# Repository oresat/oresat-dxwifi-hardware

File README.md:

# oresat-dxwifi-hardware
This repository is for the DxWiFi hardware that will fly on the OreSat satellite. DxWiFi is our communication subsystem for high speed data (1 Mbps) using 2.4 GHz WiFi between the spacecraft and ground.

This is hardware for the **satellite** only; please see the other repos if you're looking for the [OreSat Live Handheld Ground Station](https://github.com/oresat/oresat-live-handheld-ground-station) or the [Mini-OreSat testing platform for high altitude balloons](https://github.com/oresat/oresat-live-mini-oresat).

We intend to use "ordinary WiFi" (IEEE 802.11b) as a high speed satellite communication system. What is _not_ ordinary is that we run the radio under the amateur radio rules and regulations (FCC Part 97) and thus can increase power levels and antenna gains necessary to make the link budget work.

### Ordinary WiFi
The plan is to use the Qualcomm Atheros AR9271 USB to WiFi adapter because of the driver support in Linux.

### Non ordinary bi-directional power amplifier
This project is intended to operate under the Amateur Radio Service [47CFR97](https://www.gpo.gov/fdsys/pkg/CFR-1996-title47-vol5/pdf/CFR-1996-title47-vol5-part97.pdf) whereby larger power levels and higher gain directional antennas can be used within the [13 cm band](https://en.wikipedia.org/wiki/13-centimeter_band) to close the link.

NB:  There are other DxWiFi materials on the PSAS GitHub repo, but those repos are deprecated.

Link budgets can be found [here](https://github.com/oresat/oresat-dxwifi-hardware/tree/master/Link-Model).

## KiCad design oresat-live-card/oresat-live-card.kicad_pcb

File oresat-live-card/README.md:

---
title: "**OreSat Live / DxWiFi Card**"
subtitle: |
  **Fabrication and Assembly Information**\
  For build TIME-STAMP
fontsize: 10pt
geometry:
  - margin=0.5in
toc: true
toc-depth: 2
colorlinks: true
urlcolor: blue
---

\newpage

# About this Board

## Board Description

TODO: DESCRIBE CARD

## Documentation Links

- OL hardware Git repository: <https://github.com/oresat/oresat-dxwifi-hardware>
- OL software Git reposity: <https://github.com/oresat/oresat-dxwifi-software>
- **TODO:** OL Design Notes + Design Review Notes

## Documentation Files

| Filename                        | Notes                                    |
| ------------------------------- | ---------------------------------------- |
| README.pdf                      | This README file                         |
| PROJECT-NAME-outline.dxf        | Board outline (with holes) in DXF format |
| PROJECT-NAME-pcba.step          | 3D model of PCBA (with components)       |
| PROJECT-NAME-render-bot.jpg     | Render of the top of the 3D model        |
| PROJECT-NAME-render-bot.jpg     | Render of the bottom of the 3D model     |
| PROJECT-NAME-schematic.pdf      | PDF of board schematics                  |

## Contact Information

- Website: <https://www.oresat.org/>
- Email: <oresat@pdx.edu>
- Instagram: @pdxaerospace

## Board Renders

{width=50%}
{width=50%}

\newpage

# Printed Circuit Board (PCB) Fabrication Information

## Board Info

- 4 layer board
- Bounding box is 99.8 x 94.6 mm (3.93 x 3.72 in)
- Board thickness is 1.59 mm (0.063 inch)
- **Important:** See Materials and Stack Up sections below

## Board Requirements

- Design Rules
    - Minimum Trace / Space design rules
       - Outer layers: 0.127 mm (5.0 mil) / 0.127 mm (5.0 mil)
       - Inner layers: 0.127 mm (5.0 mil) / 0.127 mm (5.0 mil)
    - Outer dimension router tolerance: +/- 0.254 mm (10.0 mil)
    - Hole placement tolerance: +/- 0.075 mm (3.0 mil)
    - Inner tab routed slot tolerance: +/- 0.254 mm (10.0 mil)
- Drills
   - Drill Positional Tolerance: 0.051 mm (2.0 mil)
   - Drill Size tolerance: +/- 0.064 mm (2.5 mil)
- Plated/Un-plated holes
  - There are 6 un-plated (NPT) holes
  - There are 1477 plated through (PTH) holes
  - PTH minimum diameter: 0.254 mm (10 mil)
  - PTH minimum annulus: 0.102 mm (4 mil) radius
- Outline/Routing
  - Requires a 1.0 mm or smaller diameter routing bit
- Slots
  - There are no slots.
- Cutouts
  - There are no cutouts
- There are 3 fiducials on the top layer and 3 on the bottom layer.
- Panel tabs ("mouse bites")
   - Card edges must be smooth; no mouse bites or other intrusions into the card outline.
   - If external mouse bites are required, minimize and customer will remove by hand before assembly.
- If not otherwise specified, build to IPC 6012 Class 2 or better.

## Materials

- Controlled impedance
   - The stackup is critical for the performance of high speed signals on this board.
   - As long as the stackup is controlled, the board is not considered controlled impedance.
- Isola FR408HR or material with equivalent Dk.
- Board Surface treatment should be ENIG, althogh immersion Silver is acceptable.
- White silkscreen on top and bottom surface
- Taiyo PSR-4000 or equivalent soldermask on top and bottom, no requirements for color.

## Stack Up

| Layer         | Thickness           | Notes                                        |
|---------------|---------------------|----------------------------------------------|
| Top Copper    | 0.043 mm /  1.7 mil |  Layer 1 foil, 1 oz Cu after plating         |
| prepreg       | 0.200 mm /  7.9 mil |  Prepreg - Isola FR408HR 2113                |
| Layer 2       | 0.018 mm /  0.7 mil |  Layer 2 foil, 0.5 oz Cu                     |
| Core          | 0.991 mm /   39 mil |  Core Isola FR408HR                          |
| Layer 3       | 0.018 mm /  0.7 mil |  Layer 3 foil, 0.5 oz Cu                     |
| prepreg       | 0.200 mm /  7.9 mil |  Prepreg - Isola FR408HR 2113                |
| Bottom Copper | 0.043 mm /  1.7 mil |  Layer 4 foil, 1 oz copper after plating     |
| **Total Stackup** | **1.588 mm / 62.5 mil** |                                      |

## Array / Panel Information

- Coordinate with Contract Manufacturer (CM) for optimal size of this panel.
- If no feedback from CM, then produce single boards (no panel).

## Fabrication Files

### IPC-2581 File

| Filename                 | Notes                                   |
| ------------------------ | --------------------------------------- |
| PROJECT-NAME-ipc2581.xml | IPC-2581 board information file         |

### Legacy PCB Files

| Filename                      | Notes                                         |
| ------------------------------| --------------------------------------------- |
| PROJECT-NAME-Edge_Cuts.gbr    | RS274X file for the dimension (outline) layer |
| PROJECT-NAME-F_Silkscreen.gbr | RS274X file for the top silkscreen            |
| PROJECT-NAME-F_Mask.gbr       | RS274X file for the top soldermask            |
| PROJECT-NAME-F_Cu.gbr         | RS274X file for the top copper layer          |
| PROJECT-NAME-In1_Cu.gbr       | RS274X file for the layer 2 copper            |
| PROJECT-NAME-In2_Cu.gbr       | RS274X file for the layer 3 copper            |
| PROJECT-NAME-B_Cu.gbr         | RS274X file for the bottom copper layer       |
| PROJECT-NAME-B_Mask.gbr       | RS274X file for the bottom soldermask         |
| PROJECT-NAME-B_Silkscreen.gbr | RS274X file for the bottom silkscreen         |
| PROJECT-NAME-NPTH.drl         | Excellon file for non-plated through holes    |
| PROJECT-NAME-PTH.drl          | Excellon file for plated through holes        | 

\newpage

# Printed Circuit Board Assembly (PCBA) Information

## Assembly Info

- There are components are on the top and bottom side of the board.
- This PCBA is mostly surface mount (SMT) with a few (THT) components.

## Assembly Requirements

- Assemble to IPC Class 2 or better
- Bake components that are not moisture sealed to appropriate levels as required.
- Solder paste MUST be leaded.
- Aqueous flux and wash strongly preferred.
   - Clean to NASA Standard "Visibly Clean (VC)": No particles or residues are visible to the naked eye.
- No conformal coating.
- Ship in antistatic protective bag

## Component Specific Assembly Information

- SMPM connectors (J3, J4) should be hand-added according to the Oresat SOP.

## Assembly Files

### IPC-2581 File

| Filename                 | Notes                           |
| ------------------------ | ------------------------------- |
| PROJECT-NAME-ipc2581.xml | IPC-2581 board information file |

### Bill of Materials (BOM)

| Filename             | Description                            |
| -------------------- | -------------------------------------- |
| PROJECT-NAME-bom.csv | BOM in Comma Separated Variable format |

### Solder Paste Stencils

| Filename                 | Notes                                            |
| ------------------------ | ------------------------------------------------ |
| PROJECT-NAME-B_Paste.gbr | RS274X file for top/front solder paste stencil   |
| PROJECT-NAME-F_Paste.gbr | RS274X file for bottom/back solder paste stencil |

### Mounting/Placement Location

| Filename            | Description                                 |
| ------------------- | ------------------------------------------- |
| PROJECT-NAME-3u.pos | Pick and place locations for components     |

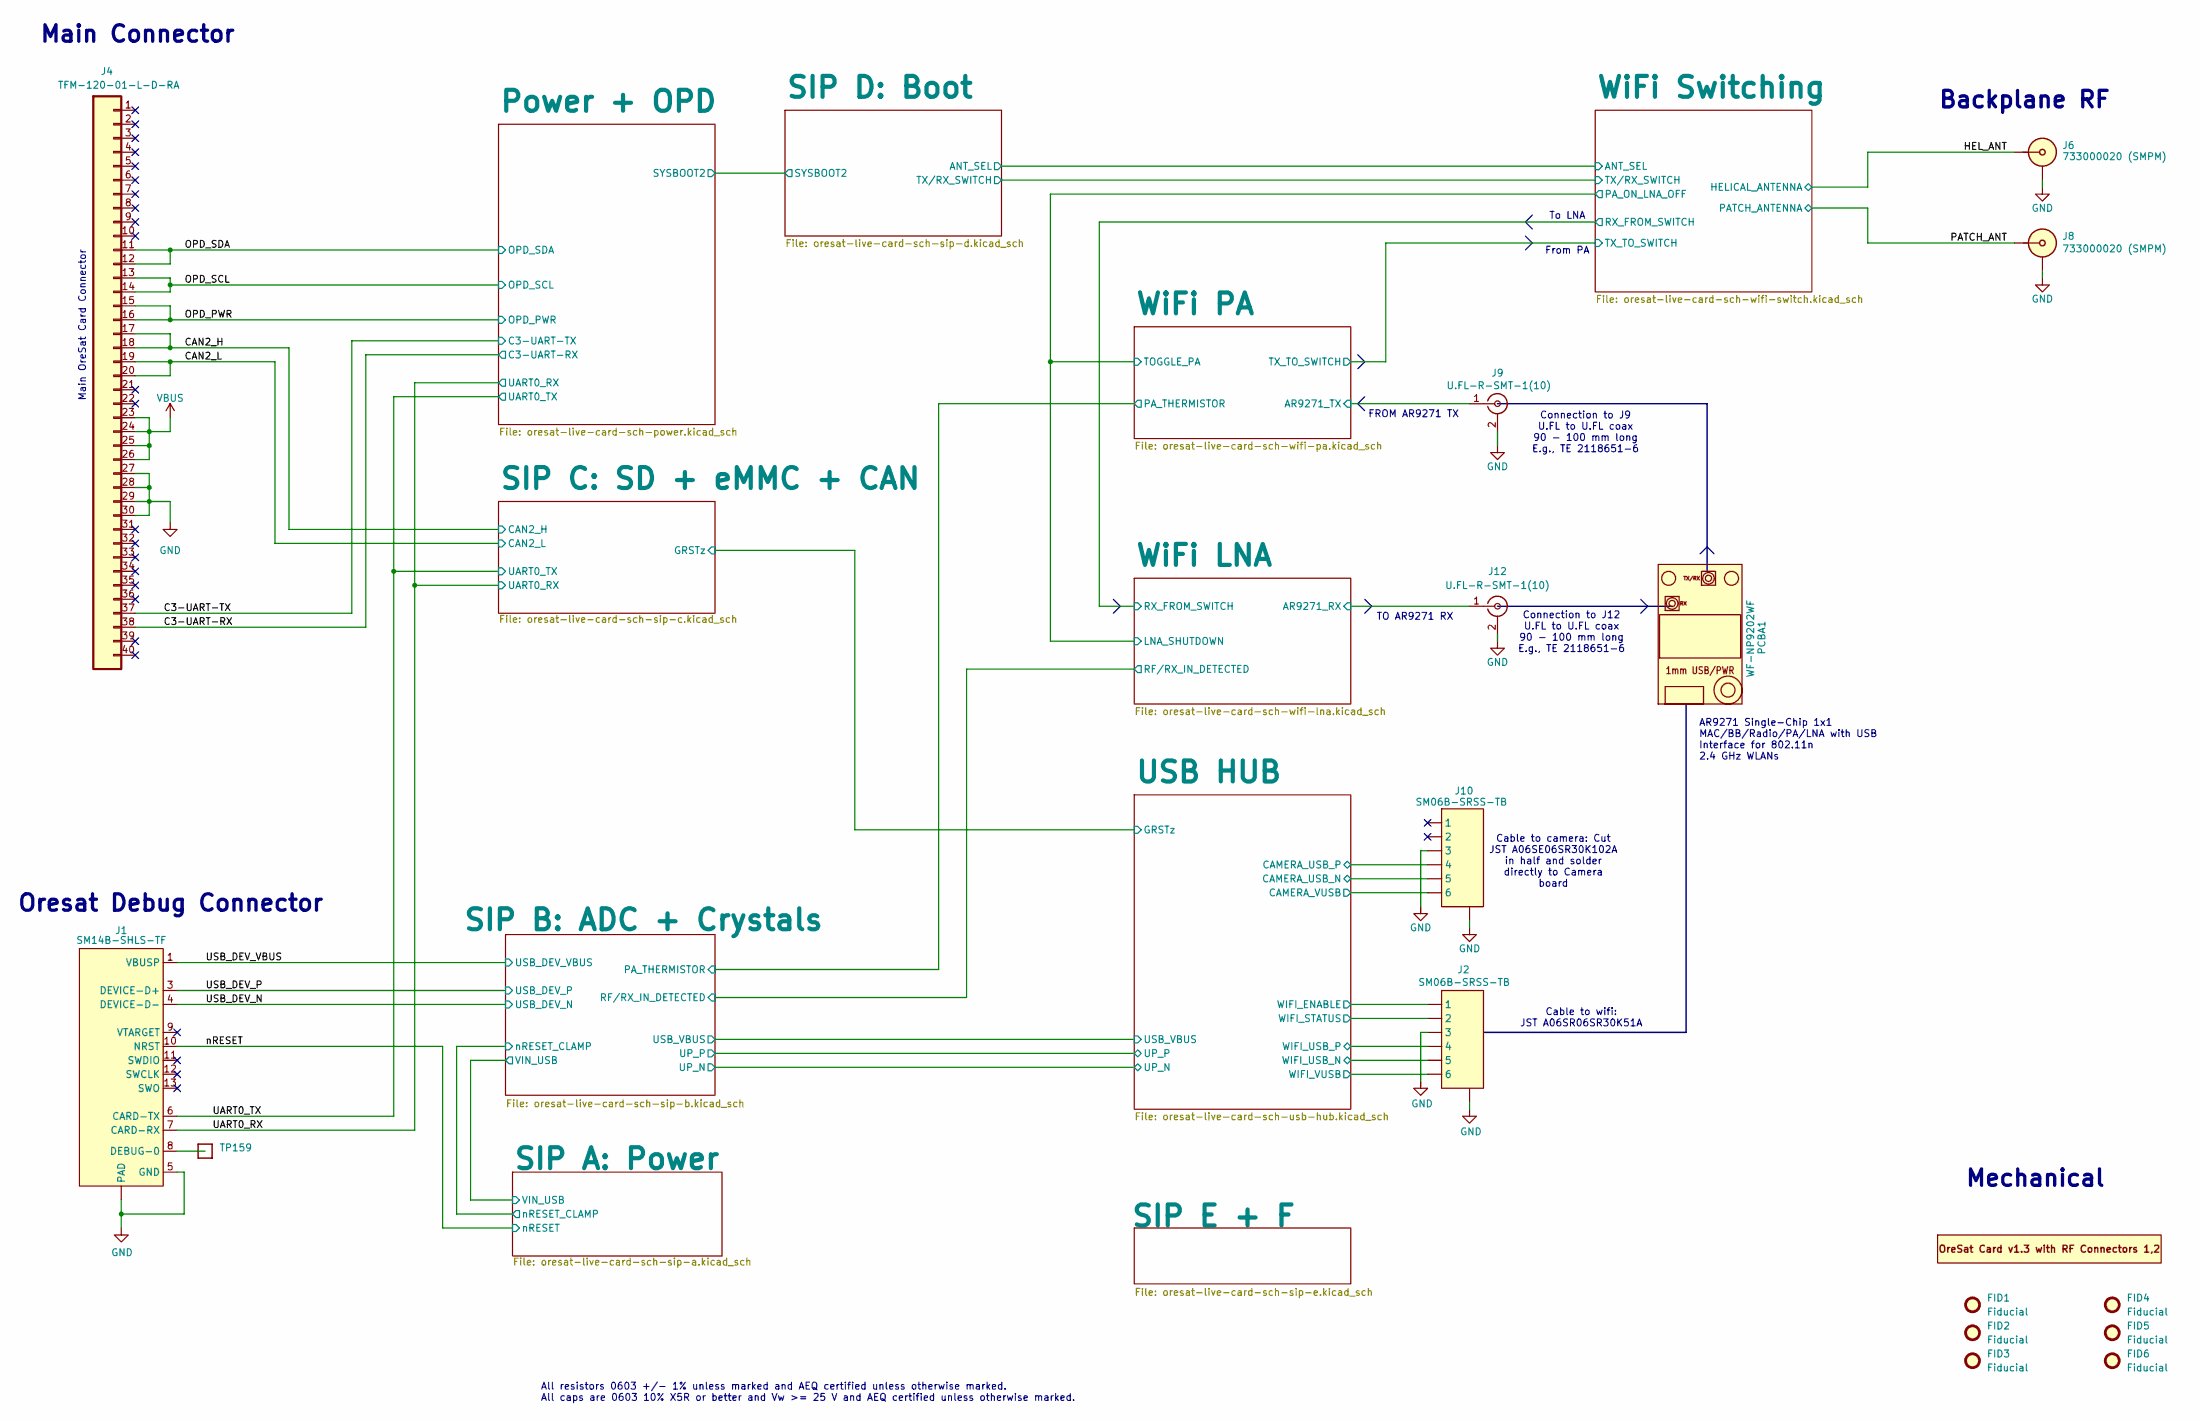
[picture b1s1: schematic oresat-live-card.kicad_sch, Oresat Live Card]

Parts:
FID1, FID2, FID3, FID4, FID5, FID6: Fiducial; Fiducial_1mm_Mask2mm
J1: SM14B-SHLS-TF; J-JST-SM14BSHLSTF; MPN SM14B-SHLS-TF
J2, J10: SM06B-SRSS-TB; CONN_SM06B-SRSS-TB_JST; MPN SM06B-SRSS-TB
J4: TFM-120-01-L-D-RA; J-SAMTEC-TFM-120-X1-XXX-D-RA; MPN TFM-120-01-L-D-RA
J6, J8: 733000020 (SMPM); J-MOLEX-SMPM-073300-002X; MPN 733000020
J9, J12: U.FL-R-SMT-1(10); U.FL_Molex_MCRF_73412-0110_Vertical; MPN U.FL-R-SMT-1(10)
PCB1: ORESAT-CARD-V1.3-GENERIC-1RF-POS1; ORESAT-CARD-V1.3-2RF-LEFT; MPN N/A
PCBA1: WF-NP9202WF; WF-NP9202; MPN WF-NP9202WF
TP159: 0.03x0.04; TestPoint-0.75mm-th

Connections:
/C3-UART-RX: J4.38; also elsewhere on the board
/C3-UART-TX: J4.37; also elsewhere on the board
/CAN2_H: J4.17, J4.18; also elsewhere on the board
/CAN2_L: J4.19, J4.20; also elsewhere on the board
/HEL_ANT: J6.1 (SIG); also elsewhere on the board
/OPD_PWR: J4.15, J4.16; also elsewhere on the board
/OPD_SCL: J4.13, J4.14; also elsewhere on the board
/OPD_SDA: J4.11, J4.12; also elsewhere on the board
/PATCH_ANT: J8.1 (SIG); also elsewhere on the board
/UART0_RX: J1.7 (CARD-RX); also elsewhere on the board
/UART0_TX: J1.6 (CARD-TX); also elsewhere on the board
/USB HUB/CAMERA_USB_N: J10.5; also elsewhere on the board
/USB HUB/CAMERA_USB_P: J10.4; also elsewhere on the board
/USB HUB/CAMERA_VUSB: J10.6; also elsewhere on the board
/USB HUB/WIFI_ENABLE: J2.1; also elsewhere on the board
/USB HUB/WIFI_STATUS: J2.2; also elsewhere on the board
/USB HUB/WIFI_USB_N: J2.5; also elsewhere on the board
/USB HUB/WIFI_USB_P: J2.4; also elsewhere on the board
/USB HUB/WIFI_VUSB: J2.6; also elsewhere on the board
/USB_DEV_N: J1.4 (DEVICE-D-); also elsewhere on the board
/USB_DEV_P: J1.3 (DEVICE-D+); also elsewhere on the board
/USB_DEV_VBUS: J1.1 (VBUSP), J1.2 (VBUSP); also elsewhere on the board
/WiFi LNA/AR9271_RX: J12.1 (In); also elsewhere on the board
/WiFi PA/AR9271_TX: J9.1 (In); also elsewhere on the board
/nRESET: J1.10 (NRST); also elsewhere on the board
GND: J1.5 (GND), J1.14 (GND), J1.15 (PAD), J1.16 (PAD), J2.3, J2.7, J2.8 (7), J4.27, J4.28, J4.29, J4.30, J6.2 (SHLD), J8.2 (SHLD), J9.2 (Ext), J10.3, J10.7, J10.8 (7), J12.2 (Ext); also elsewhere on the board
unnamed: J1.8 (DEBUG-0), TP159.1 (1_1)
VBUS: J4.23, J4.24, J4.25, J4.26; also elsewhere on the board

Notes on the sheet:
Mechanical
All resistors 0603 +/- 1% unless marked and AEQ certified unless otherwise marked. All caps are 0603 10% X5R or better and Vw >= 25 V and AEQ certified unless otherwise marked.
TO AR9271 RX
Main Connector
Main OreSat Card Connector
FROM AR9271 TX
From PA
Connection to J12 U.FL to U.FL coax 90 - 100 mm long E.g., TE 2118651-6
Connection to J9 U.FL to U.FL coax 90 - 100 mm long E.g., TE 2118651-6
AR9271 Single-Chip 1x1 MAC/BB/Radio/PA/LNA with USB Interface for 802.11n 2.4 GHz WLANs
To LNA
Cable to wifi: JST A06SR06SR30K51A
Cable to camera: Cut JST A06SE06SR30K102A in half and solder directly to Camera board
Oresat Debug Connector
Backplane RF

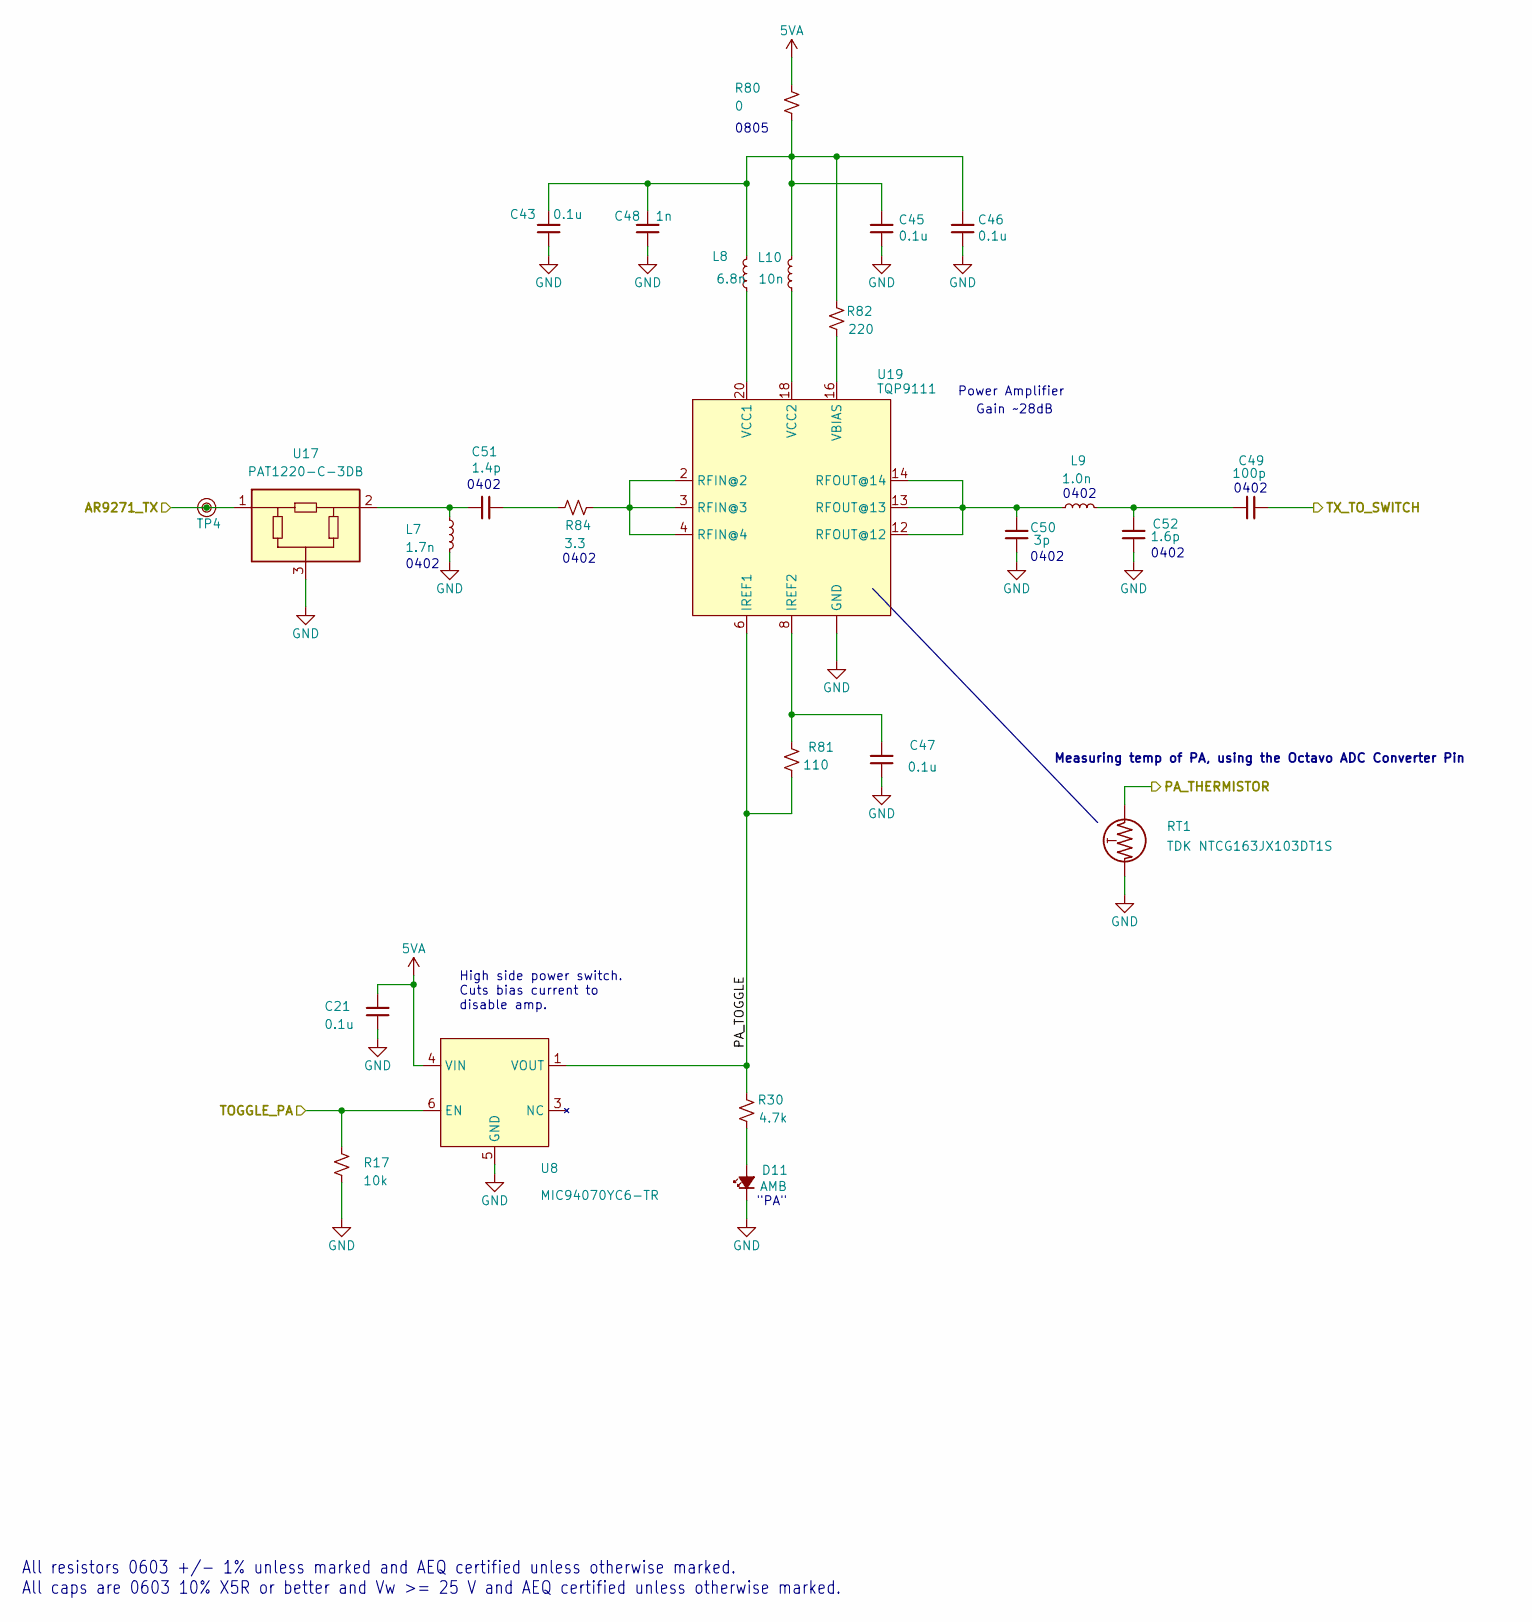
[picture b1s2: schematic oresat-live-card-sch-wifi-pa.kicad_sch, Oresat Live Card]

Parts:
C21, C43, C45, C46, C47: 0.1u; 0603-C-NOSILK; MPN C0603C104K5RACAUTO
C48: 1n; 0402-C-NOSILK; MPN C0402C102J1GACTU
C49: 100p; 0402-C-NOSILK; MPN GCM1555C1H101GA16D
C50: 3p; 0402-C-NOSILK; MPN 04025U3R0BAT2A
C51: 1.4p; 0402-C-NOSILK; MPN 04025J1R1PBSTR\500
C52: 1.6p; 0402-C-NOSILK; MPN 04025U1R6BAT2A
D11: AMB; LED-0603; MPN 150060AS75000
L7: 1.7n; 0402-C-NOSILK; MPN 0402DC-1N7XJRW
L8: 6.8n; 0805-C-NOSILK; MPN 0805CS-060XJRC
L9: 1.0n; 0402-C-NOSILK; MPN MLK1005S1N0ST000
L10: 10n; INDC2928X203N; MPN 1008HQ-10NXJLC
R17: 10k; 0603-C-NOSILK; MPN RMCF0603FT10K0
R30: 4.7k; 0603-C-NOSILK; MPN RMCF0603FT4K70
R80: 0; 0805-C-NOSILK; MPN RMCF0805ZT0R00
R81: 110; 0402-C-NOSILK; MPN RMCF0402FT110R
R82: 220; 0603-C-NOSILK; MPN RMCF0603FT110R
R84: 3.3; 0402-C-NOSILK; MPN CRCW04023R30FKED
RT1: TDK NTCG163JX103DT1S; 0603-THERMISTOR-B; MPN NTCG163JX103DT1S
TP4: TestPoint_RF_Probe
U8: MIC94070YC6-TR; SC-70-6_MCH; MPN MIC94070YC6-TR
U17: PAT1220-C-3DB; RF_Attenuator_Susumu_PAT1220; MPN PAT1220-C-3DB-T5
U19: TQP9111; QFN50P400X400X102-21N; MPN TQP9111

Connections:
5VA: C21.1, R80.2, U8.4 (VIN); also elsewhere on the board
/SIP B: ADC + Crystals/PA_THERMISTOR: RT1.1; also elsewhere on the board
/WiFi LNA/LNA_SHUTDOWN: R17.2, U8.6 (EN); also elsewhere on the board
/WiFi PA/AR9271_TX: TP4.1 (1_1), U17.1; also elsewhere on the board
/WiFi PA/PA_TOGGLE: R30.1, R81.1, U8.1 (VOUT), U19.6 (IREF1)
/WiFi PA/TX_TO_SWITCH: C49.2; also elsewhere on the board
GND: C21.2, C43.2, C45.2, C46.2, C47.2, C48.2, C50.2, C52.2, D11.1 (K), L7.1, R17.1, RT1.2, U8.2 (GND), U8.5 (GND), U17.3, U19.1 (GND), U19.5 (GND), U19.7 (GND), U19.9 (GND), U19.10 (GND), U19.11 (GND), U19.15 (GND), U19.17 (GND), U19.19 (GND), U19.21 (GND); also elsewhere on the board
unnamed: C43.1, C45.1, C46.1, C48.1, L8.2, L10.2, R80.1, R82.2
unnamed: C49.1, C52.1, L9.2
unnamed: C51.1, L7.2, U17.2
unnamed: C51.2, R84.1
unnamed: D11.2 (A), R30.2
unnamed: C47.1, R81.2, U19.8 (IREF2)
unnamed: R84.2, U19.2 (RFIN@2), U19.3 (RFIN@3), U19.4 (RFIN@4)
unnamed: C50.1, L9.1, U19.12 (RFOUT@12), U19.13 (RFOUT@13), U19.14 (RFOUT@14)
unnamed: R82.1, U19.16 (VBIAS)
unnamed: L8.1, U19.20 (VCC1)
unnamed: L10.1, U19.18 (VCC2)

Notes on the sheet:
0402
"PA"
High side power switch. Cuts bias current to disable amp.
Gain ~28dB
0805
Measuring temp of PA, using the Octavo ADC Converter Pin
Power Amplifier
All resistors 0603 +/- 1% unless marked and AEQ certified unless otherwise marked. All caps are 0603 10% X5R or better and Vw >= 25 V and AEQ certified unless otherwise marked.

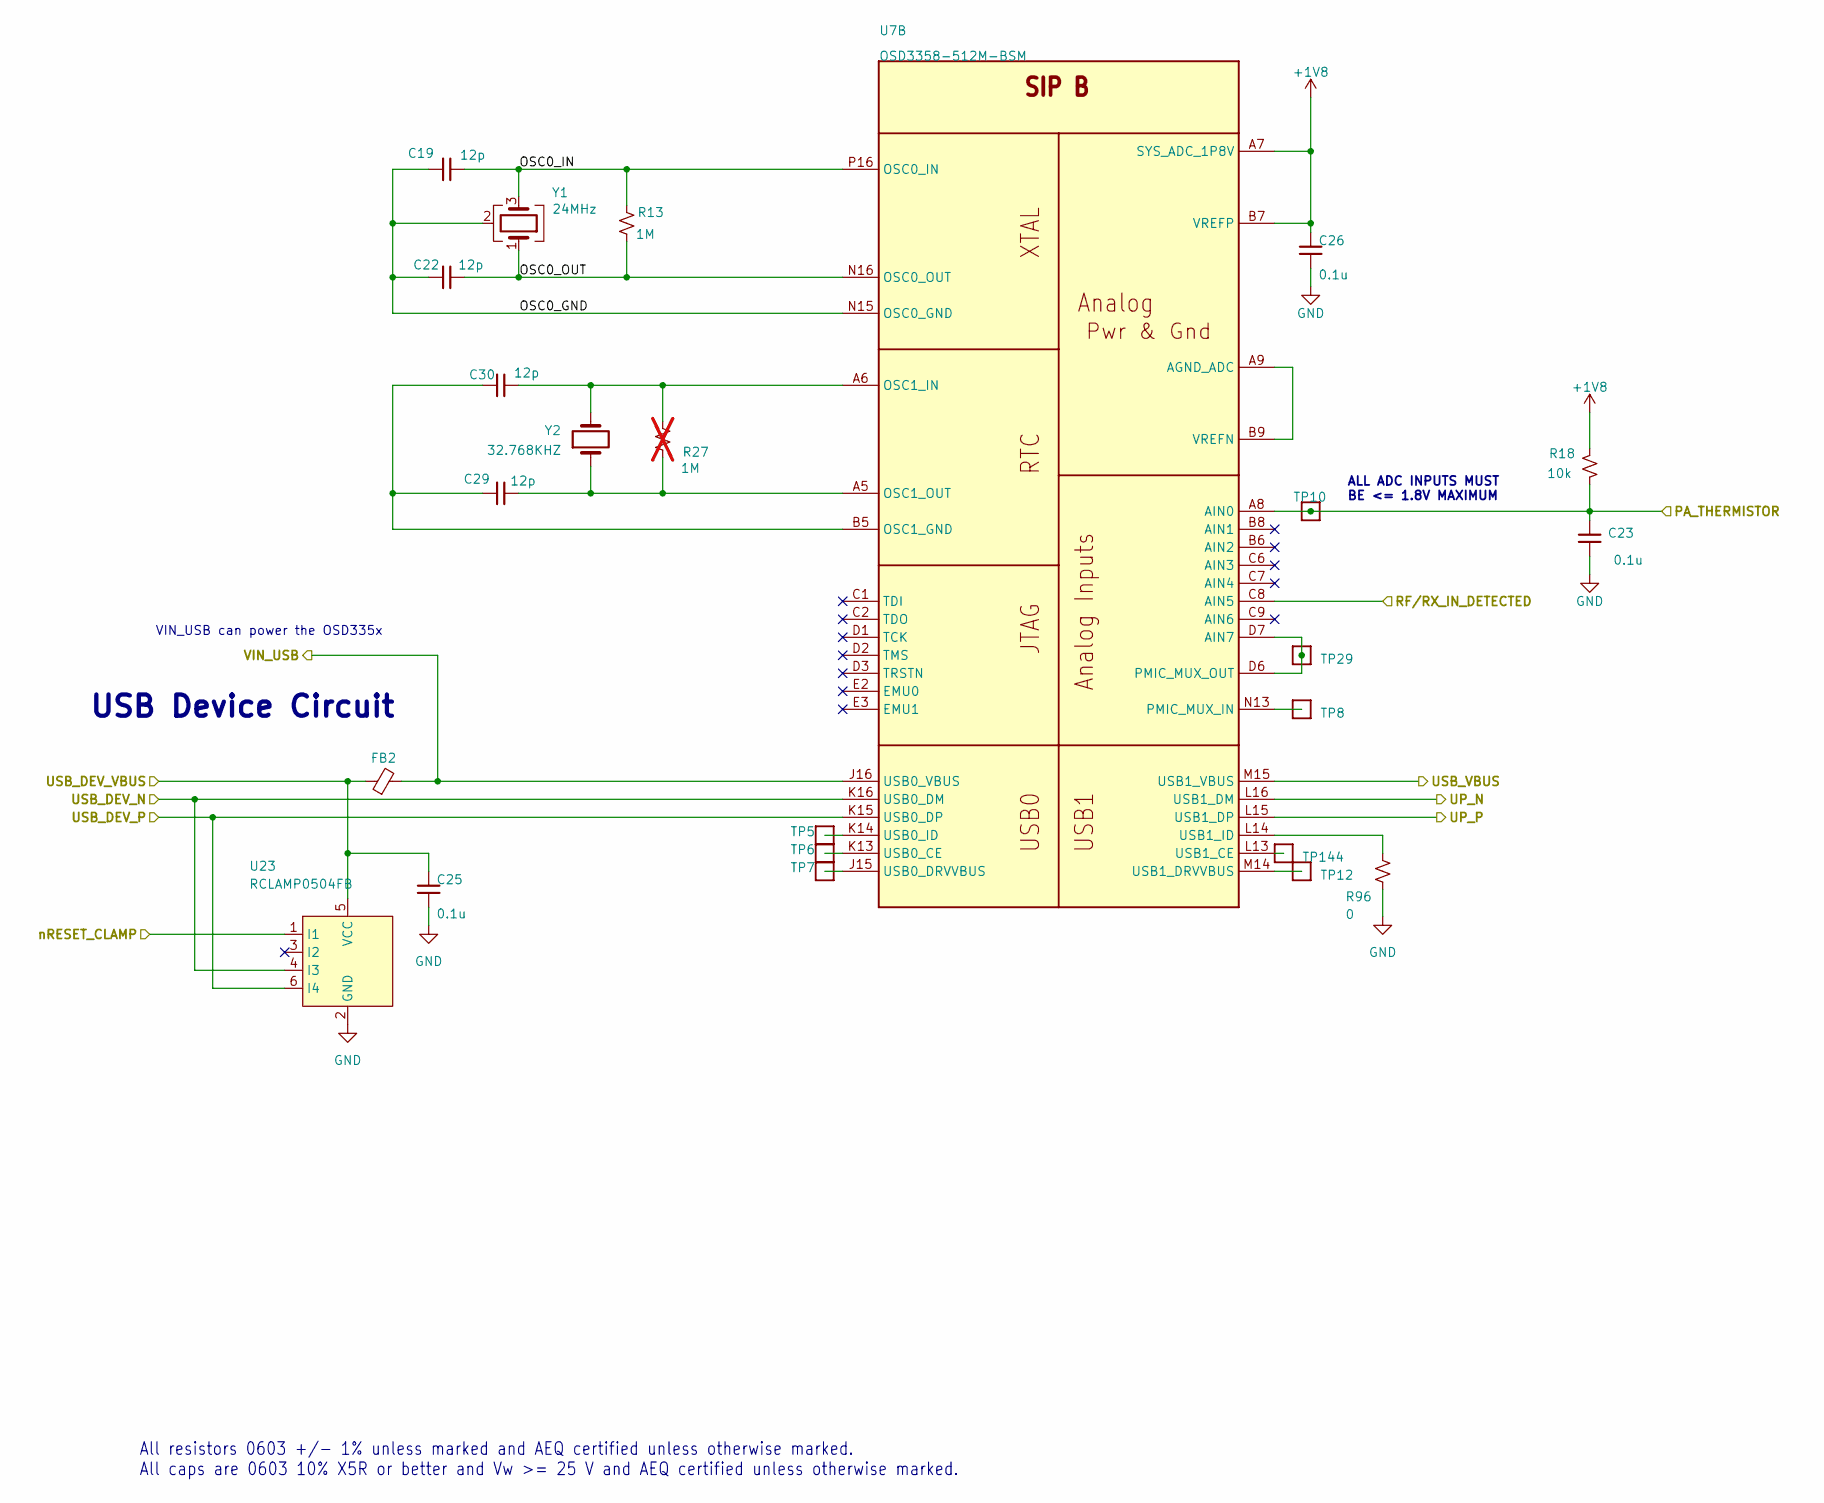
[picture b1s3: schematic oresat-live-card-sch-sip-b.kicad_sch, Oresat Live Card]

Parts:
C19, C22, C29, C30: 12p; 0603-C-NOSILK; MPN C0603C120J1GACTU
C23, C25, C26: 0.1u; 0603-C-NOSILK; MPN C0603C104K5RACAUTO
FB2: BLM18KG300TH1D; 0603; MPN BLM18KG300JH1D
R13: 1M; 0603-C-NOSILK; MPN RMCF0603FT1M00
R18: 10k; 0603-C-NOSILK; MPN RMCF0603FT10K0
R27: 1M; R_0603_1608Metric; not fitted
R96: 0; 0603-C-NOSILK; MPN RMCF0603ZT0R00
TP5, TP6, TP7, TP12, TP144: TEST-POINT3X4; TestPoint_Pad_D1.0mm
TP8, TP10, TP29: TEST-POINT; TestPoint_Pad_D1.0mm
U7: OSD3358-512M-BSM; U-Octavo-OSD335X-BGA-256; MPN OSD3358-512M-BSM
U23: RCLAMP0504FB; SC70-6; MPN RCLAMP0504FBTCT
Y1: 24MHz; 5X3.2-4SMD; MPN ECS-240-12-30BQ-AEN-TR
Y2: 32.768KHZ; CRYSTAL_3.2X1.5; MPN ABS07-32.768KHZ-T

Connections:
+1V8: C26.1, R18.2, U7.A7 (SYS_ADC_1P8V), U7.B7 (VREFP)
/SIP A: Power/VIN_USB: FB2.2, U7.J16 (USB0_VBUS); also elsewhere on the board
/SIP A: Power/nRESET_CLAMP: U23.1 (I1); also elsewhere on the board
/SIP B: ADC + Crystals/OSC0_GND: C19.1, C22.1, U7.N15 (OSC0_GND), Y1.2 (G), Y1.4 (G)
/SIP B: ADC + Crystals/OSC0_IN: C19.2, R13.2, U7.P16 (OSC0_IN), Y1.3
/SIP B: ADC + Crystals/OSC0_OUT: C22.2, R13.1, U7.N16 (OSC0_OUT), Y1.1
/SIP B: ADC + Crystals/PA_THERMISTOR: C23.1, R18.1, TP10.1 (1_1), U7.A8 (AIN0); also elsewhere on the board
/SIP B: ADC + Crystals/RF/RX_IN_DETECTED: U7.C8 (AIN5); also elsewhere on the board
/SIP B: ADC + Crystals/UP_N: U7.L16 (USB1_DM); also elsewhere on the board
/SIP B: ADC + Crystals/UP_P: U7.L15 (USB1_DP); also elsewhere on the board
/SIP B: ADC + Crystals/USB_VBUS: U7.M15 (USB1_VBUS); also elsewhere on the board
/USB_DEV_N: U7.K16 (USB0_DM), U23.4 (I3); also elsewhere on the board
/USB_DEV_P: U7.K15 (USB0_DP), U23.6 (I4); also elsewhere on the board
/USB_DEV_VBUS: C25.1, FB2.1, U23.5 (VCC); also elsewhere on the board
GND: C23.2, C25.2, C26.2, R96.1, U23.2 (GND); also elsewhere on the board
unnamed: U7.A9 (AGND_ADC), U7.B9 (VREFN)
unnamed: TP29.1 (1_1), U7.D6 (PMIC_MUX_OUT), U7.D7 (AIN7)
unnamed: C29.2, C30.2, U7.B5 (OSC1_GND)
unnamed: C30.1, R27.2, U7.A6 (OSC1_IN), Y2.2
unnamed: C29.1, R27.1, U7.A5 (OSC1_OUT), Y2.1
unnamed: TP8.1 (1_1), U7.N13 (PMIC_MUX_IN)
unnamed: TP6.1 (1_1), U7.K13 (USB0_CE)
unnamed: TP7.1 (1_1), U7.J15 (USB0_DRVVBUS)
unnamed: TP5.1 (1_1), U7.K14 (USB0_ID)
unnamed: TP144.1 (1_1), U7.L13 (USB1_CE)
unnamed: TP12.1 (1_1), U7.M14 (USB1_DRVVBUS)
unnamed: R96.2, U7.L14 (USB1_ID)

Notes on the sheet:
USB Device Circuit
VIN_USB can power the OSD335x
All resistors 0603 +/- 1% unless marked and AEQ certified unless otherwise marked. All caps are 0603 10% X5R or better and Vw >= 25 V and AEQ certified unless otherwise marked.
ALL ADC INPUTS MUST BE <= 1.8V MAXIMUM

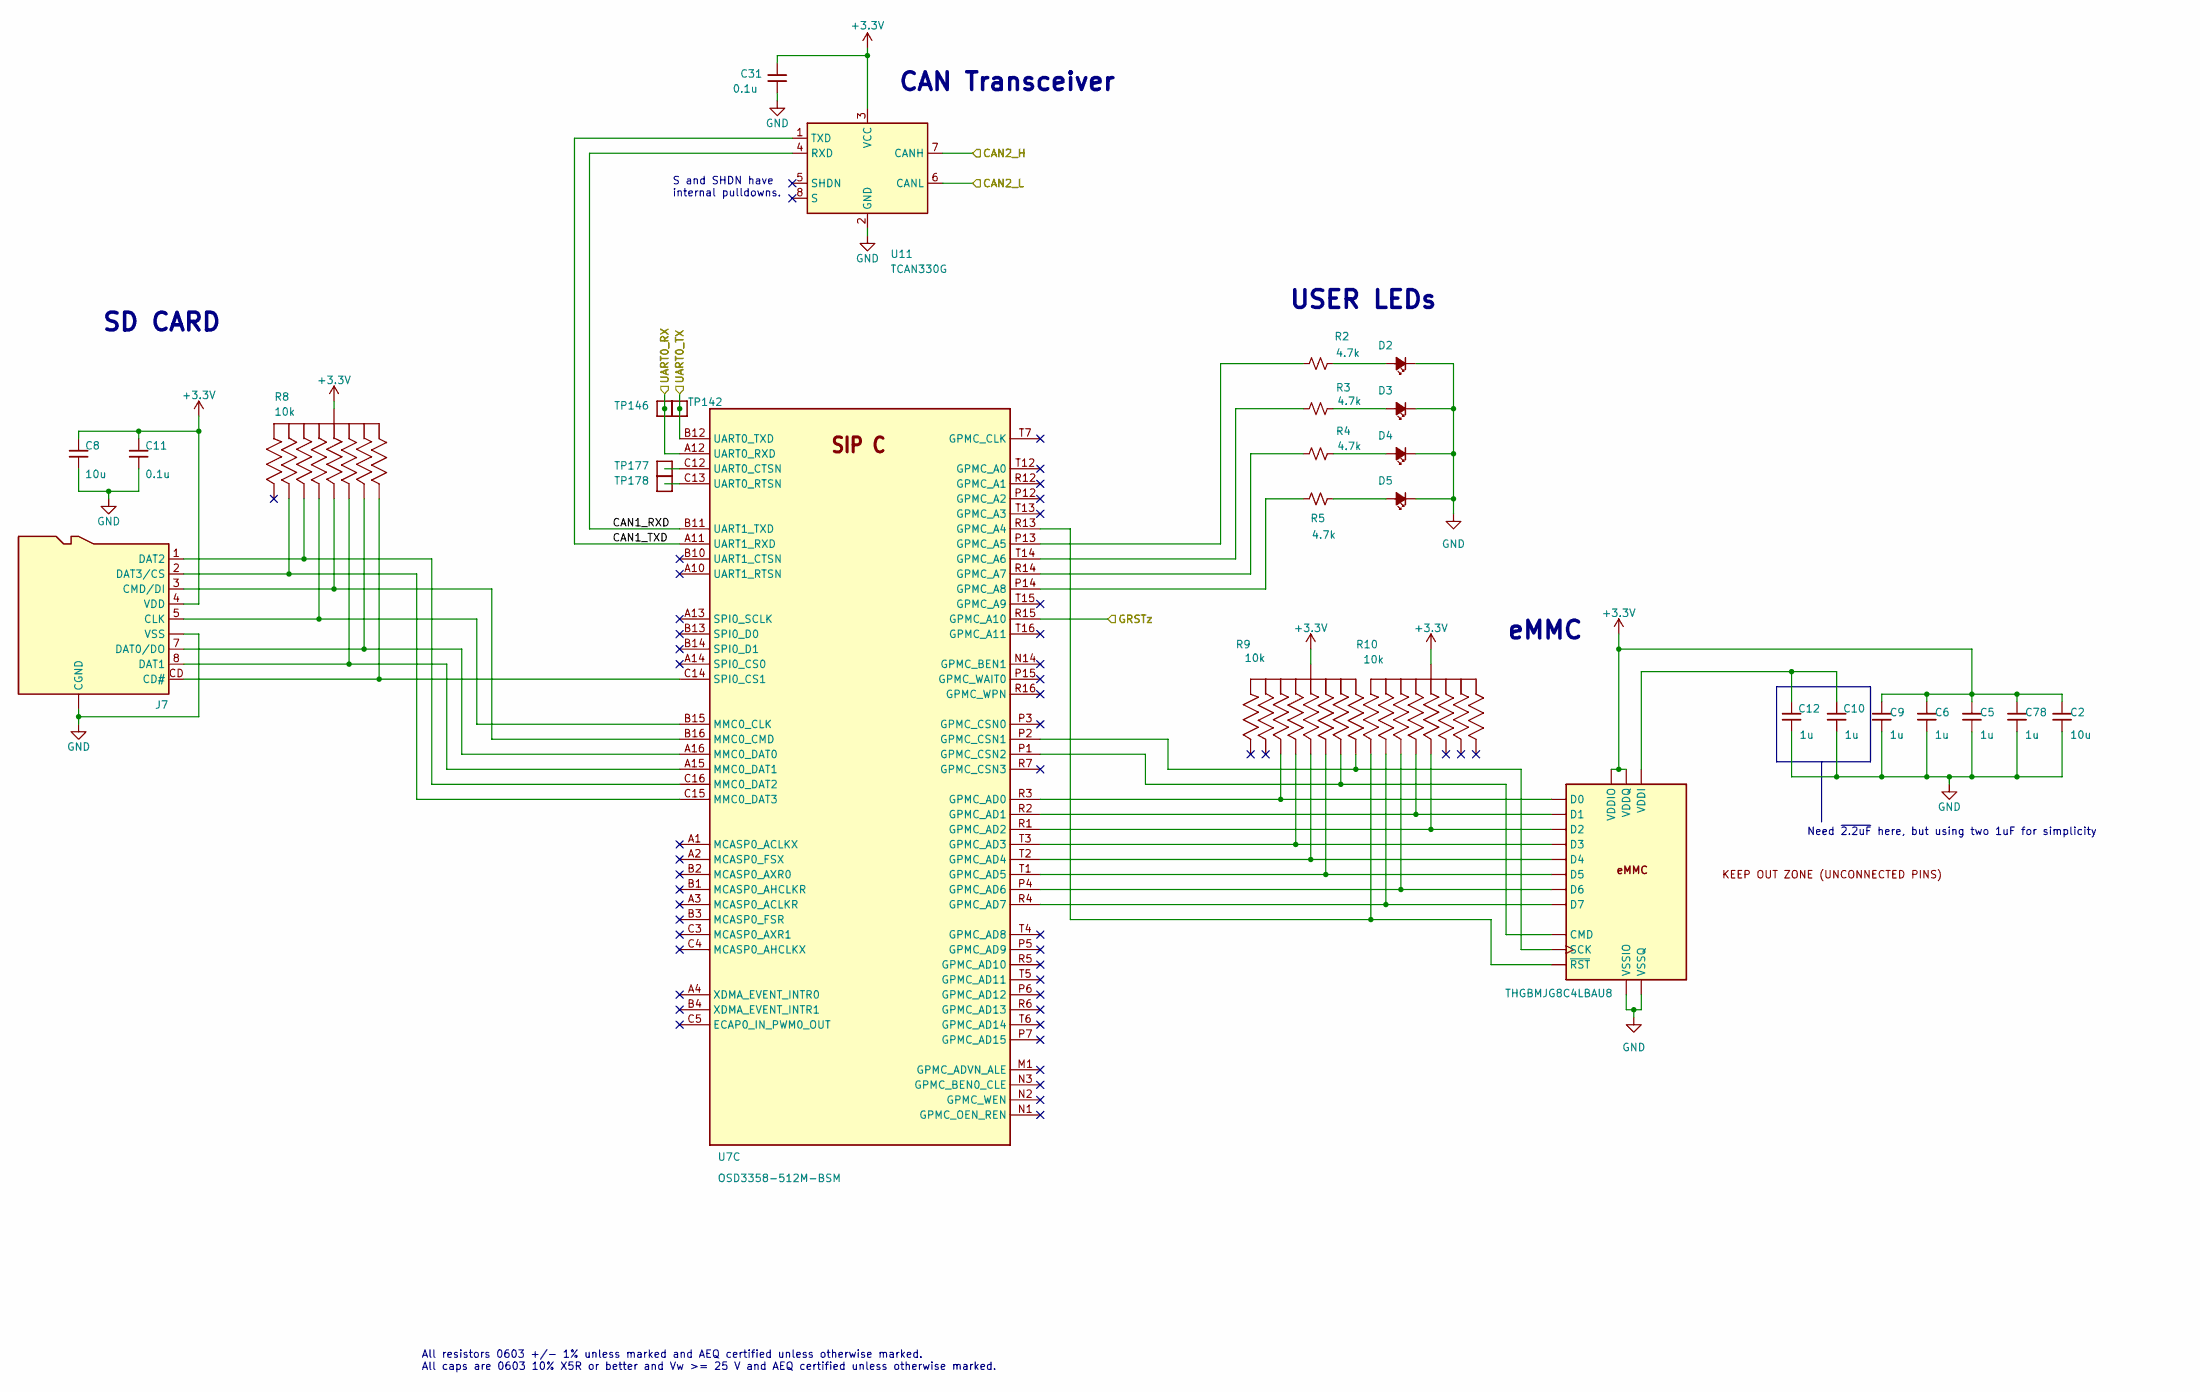
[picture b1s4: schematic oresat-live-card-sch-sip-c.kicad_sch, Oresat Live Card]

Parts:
C2, C8: 10u; 0805-C-NOSILK; MPN GRT21BC71E106KE13K
C5, C6, C9, C10, C12, C78: 1u; 0603-C-NOSILK; MPN GRT188R71E105KE13D
C11, C31: 0.1u; 0603-C-NOSILK; MPN C0603C104K5RACAUTO
D2, D3, D4, D5: BLU; LED-0603; MPN 150060BS75000
J7: DM3BT-DSF-PEJS; J-Hirose-DM3BT-DSF-PEJS; MPN DM3BT-DSF-PEJS
R2, R3, R4, R5: 4.7k; 0603-C-NOSILK; MPN RMCF0603FT4K70
R8, R9, R10: 10k; ARRAY_EXBA-M; MPN EXB-A10P103J
TP142, TP146: TEST-POINT3X4; TestPoint-0.75mm-th
TP177, TP178: TEST-POINT3X4; TestPoint_Pad_D1.0mm
U3: THGBMJG8C4LBAU8; BGA-153(11.5X13)(EMMC-BA); MPN THGBMJG8C4LBAU8
U7: OSD3358-512M-BSM; U-Octavo-OSD335X-BGA-256; MPN OSD3358-512M-BSM
U11: TCAN330G; SOT23-8_TI-DCN; MPN TCAN330GDCNR

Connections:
+3.3V: C2.1, C5.1, C6.1, C8.1, C9.1, C11.1, C31.2, C78.1, J7.4 (VDD), R8.5 (55), R8.10 (55), R9.5 (55), R9.10 (55), R10.5 (55), R10.10 (55), U3.C6 (VDDQ), U3.E6 (VDDIO), U3.F5 (VDDIO), U3.J10 (VDDIO), U3.K9 (VDDIO), U3.M4 (VDDQ), U3.N4 (VDDQ), U3.P3 (VDDQ), U3.P5 (VDDQ), U11.3 (VCC); also elsewhere on the board
/CAN2_H: U11.7 (CANH); also elsewhere on the board
/CAN2_L: U11.6 (CANL); also elsewhere on the board
/SIP C: SD + eMMC + CAN/CAN1_RXD: U7.B11 (UART1_TXD), U11.4 (RXD)
/SIP C: SD + eMMC + CAN/CAN1_TXD: U7.A11 (UART1_RXD), U11.1 (TXD)
/SIP C: SD + eMMC + CAN/GRSTz: U7.R15 (GPMC_A10); also elsewhere on the board
/UART0_RX: TP146.1 (1_1), U7.A12 (UART0_RXD); also elsewhere on the board
/UART0_TX: TP142.1 (1_1), U7.B12 (UART0_TXD); also elsewhere on the board
GND: C2.2, C5.2, C6.2, C8.2, C9.2, C10.2, C11.2, C12.2, C31.1, C78.2, D2.1 (K), D3.1 (K), D4.1 (K), D5.1 (K), J7.6 (VSS), J7.CGND1 (CGND), J7.CGND2 (CGND), J7.CGND3 (CGND), J7.CGND4 (CGND), J7.CGND5 (CGND), J7.CGND6 (CGND), J7.GND (VSS), U3.A6 (VSSIO), U3.C4 (VSSQ), U3.E7 (VSSIO), U3.G5 (VSSIO), U3.H10 (VSSIO), U3.J5 (VSSIO), U3.K8 (VSSIO), U3.N2 (VSSQ), U3.N5 (VSSQ), U3.P4 (VSSQ), U3.P6 (VSSQ), U11.2 (GND); also elsewhere on the board
unnamed: D2.2 (A), R2.2
unnamed: D3.2 (A), R3.2
unnamed: D4.2 (A), R4.2
unnamed: D5.2 (A), R5.2
unnamed: J7.CD (CD#), R8.6 (66), U7.C14 (SPI0_CS1)
unnamed: J7.5 (CLK), R8.8 (88), U7.B15 (MMC0_CLK)
unnamed: J7.3 (CMD/DI), R8.3 (33), U7.B16 (MMC0_CMD)
unnamed: J7.7 (DAT0/DO), R8.4 (44), U7.A16 (MMC0_DAT0)
unnamed: J7.8 (DAT1), R8.7 (77), U7.A15 (MMC0_DAT1)
unnamed: J7.1 (DAT2), R8.2 (22), U7.C16 (MMC0_DAT2)
unnamed: J7.2 (DAT3/CS), R8.9 (99), U7.C15 (MMC0_DAT3)
unnamed: R9.2 (22), U3.A3 (D0), U7.R3 (GPMC_AD0)
unnamed: R9.3 (33), U3.B3 (D4), U7.T2 (GPMC_AD4)
unnamed: R9.4 (44), U3.M5 (CMD), U7.P1 (GPMC_CSN2)
unnamed: R9.6 (66), U3.M6 (SCK), U7.P2 (GPMC_CSN1)
unnamed: R9.7 (77), U3.B4 (D5), U7.T1 (GPMC_AD5)
unnamed: R9.8 (88), U3.B2 (D3), U7.T3 (GPMC_AD3)
unnamed: R10.1 (11), U3.K5 (~RST), U7.R13 (GPMC_A4)
unnamed: R10.2 (22), U3.B5 (D6), U7.P4 (GPMC_AD6)
unnamed: R10.3 (33), U3.A5 (D2), U7.R1 (GPMC_AD2)
unnamed: R10.8 (88), U3.A4 (D1), U7.R2 (GPMC_AD1)
unnamed: R10.9 (99), U3.B6 (D7), U7.R4 (GPMC_AD7)
unnamed: C10.1, C12.1, U3.C2 (VDDI)
unnamed: R2.1, U7.P13 (GPMC_A5)
unnamed: R3.1, U7.T14 (GPMC_A6)
unnamed: R4.1, U7.R14 (GPMC_A7)
unnamed: R5.1, U7.P14 (GPMC_A8)
unnamed: TP177.1 (1_1), U7.C12 (UART0_CTSN)
unnamed: TP178.1 (1_1), U7.C13 (UART0_RTSN)

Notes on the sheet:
CAN Transceiver
USER LEDs
S and SHDN have internal pulldowns.
Need ~{2.2uF} here, but using two 1uF for simplicity
All resistors 0603 +/- 1% unless marked and AEQ certified unless otherwise marked. All caps are 0603 10% X5R or better and Vw >= 25 V and AEQ certified unless otherwise marked.
eMMC
SD CARD
